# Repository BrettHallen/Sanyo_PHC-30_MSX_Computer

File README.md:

# Sanyo PHC-30 MSX Computer
Information about the 三洋 Sanyo PHC-30/PHC-30N computer.

## Specifications
- Sharp LH0080A Z80 CPU
- Fujitsu MB64H120 gate array (mask code Z03?)
- Mitsubishi M5L8255AP-5 peripheral interface (PPI)
- Hitachi HN613256P 32Kbit ROM (mask code Y00)
- General Instruments AY-3-8910 Programmable Sound Generator (PSG)
- 8 x Fujitsu MB8264A-15 64K x 1-bit main DRAM (64KB)
- TI TMS9118NL Video Display Processor (VDP)
- 2 x TI TMS4416-20NL 16K x 4-bit video DRAM (16KB)

## YouTube Videos
- [Part 1: Initial Look](https://youtu.be/X6lxfxol4aE)
- [Part 2: Pico9918 & Keyboard Refurbish](https://youtu.be/wInAnoi41x8)

## TMS9118 Replacement
I replaced the TMS9118 with a [Pico9918](https://github.com/visrealm/pico9918).  I had to de-solder the TMS9118 but it came out with a little gentle coaxing - I used my ENGINEER SS-03 Solder Sucker.<br>

There is one small issue: blank screen when doing a warm restart by pressing the RESET button but Troy has already sent me some test firmware to try out.<br>

## [Replacement Power Supply](/Sanyo_PHC-30_PSU)
My attempt at a "universal" 12VDC power supply to replace the original Japanese 100VAC power supply.<br>

The original power supply generates +5VDC and ±12VDC.<br>

My replacement generates the +5VDC and -12VDC via regulators and passes through the remaining 12VDC, so a good quality, regulated, 12VDC power supply rated at 3-4A should be used.<br>

It's currently pending testing.<br>

## [Images](/Images)
Images of the computer, motherboard & chips.

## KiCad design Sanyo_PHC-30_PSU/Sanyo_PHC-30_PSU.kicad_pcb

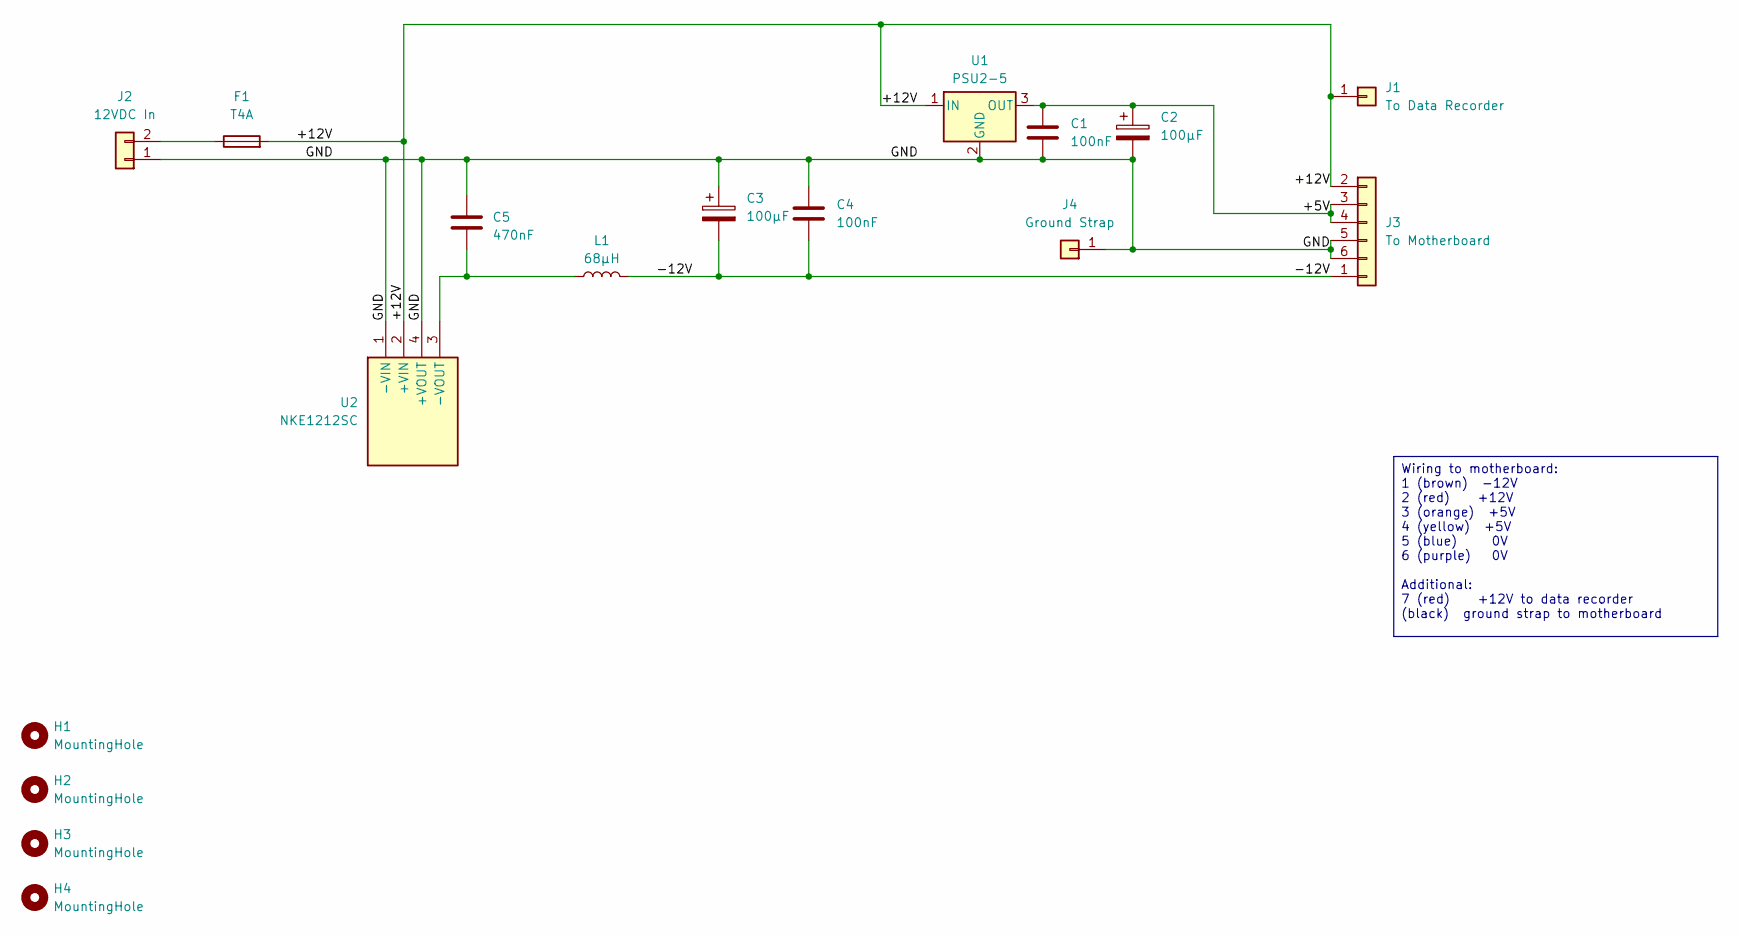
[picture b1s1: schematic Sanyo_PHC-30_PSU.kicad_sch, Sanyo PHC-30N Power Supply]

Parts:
C1, C4: 100nF; C_Disc_D3.4mm_W2.1mm_P2.50mm
C2, C3: 100µF; CP_Radial_D5.0mm_P2.50mm
C5: 470nF; C_Disc_D3.4mm_W2.1mm_P2.50mm
F1: T4A; Fuseholder_Clip-5x20mm_Littelfuse_111_Inline_P20.00x5.00mm_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
H1, H2, H3, H4: MountingHole; MountingHole_3.2mm_M3
J1: To Data Recorder; PinHeader_1x01_P2.54mm_Vertical
J2: 12VDC In; JST_VH_B2P-VH_1x02_P3.96mm_Vertical
J3: To Motherboard; JST_VH_B6P-VH_1x06_P3.96mm_Vertical
J4: Ground Strap; PinHeader_1x01_P2.54mm_Vertical
L1: 68µH; 22R683C
U1: PSU2-5; TO-220-3_Horizontal_TabDown
U2: NKE1212SC; Manufacturer_Part_Number NKE1212SC

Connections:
/+5V: C1.1, C2.1, J3.3 (+5V), J3.4 (+5V), U1.3 (OUT)
/+12V: F1.2, J1.1, J3.2 (+12V), U1.1 (IN), U2.2 (+VIN)
/-12V: C3.2, C4.2, J3.1 (-12V), L1.2
/GND: C1.2, C2.2, C3.1, C4.1, C5.2, J2.1, J3.5 (0V), J3.6 (0V), J4.1, U1.2 (GND), U2.1 (-VIN), U2.4 (+VOUT)
unnamed: F1.1, J2.2
unnamed: C5.1, L1.1, U2.3 (-VOUT)

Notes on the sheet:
Wiring to motherboard: 1 (brown) -12V 2 (red) +12V 3 (orange) +5V 4 (yellow) +5V 5 (blue) 0V 6 (purple) 0V Additional: 7 (red) +12V to data recorder (black) ground strap to motherboard

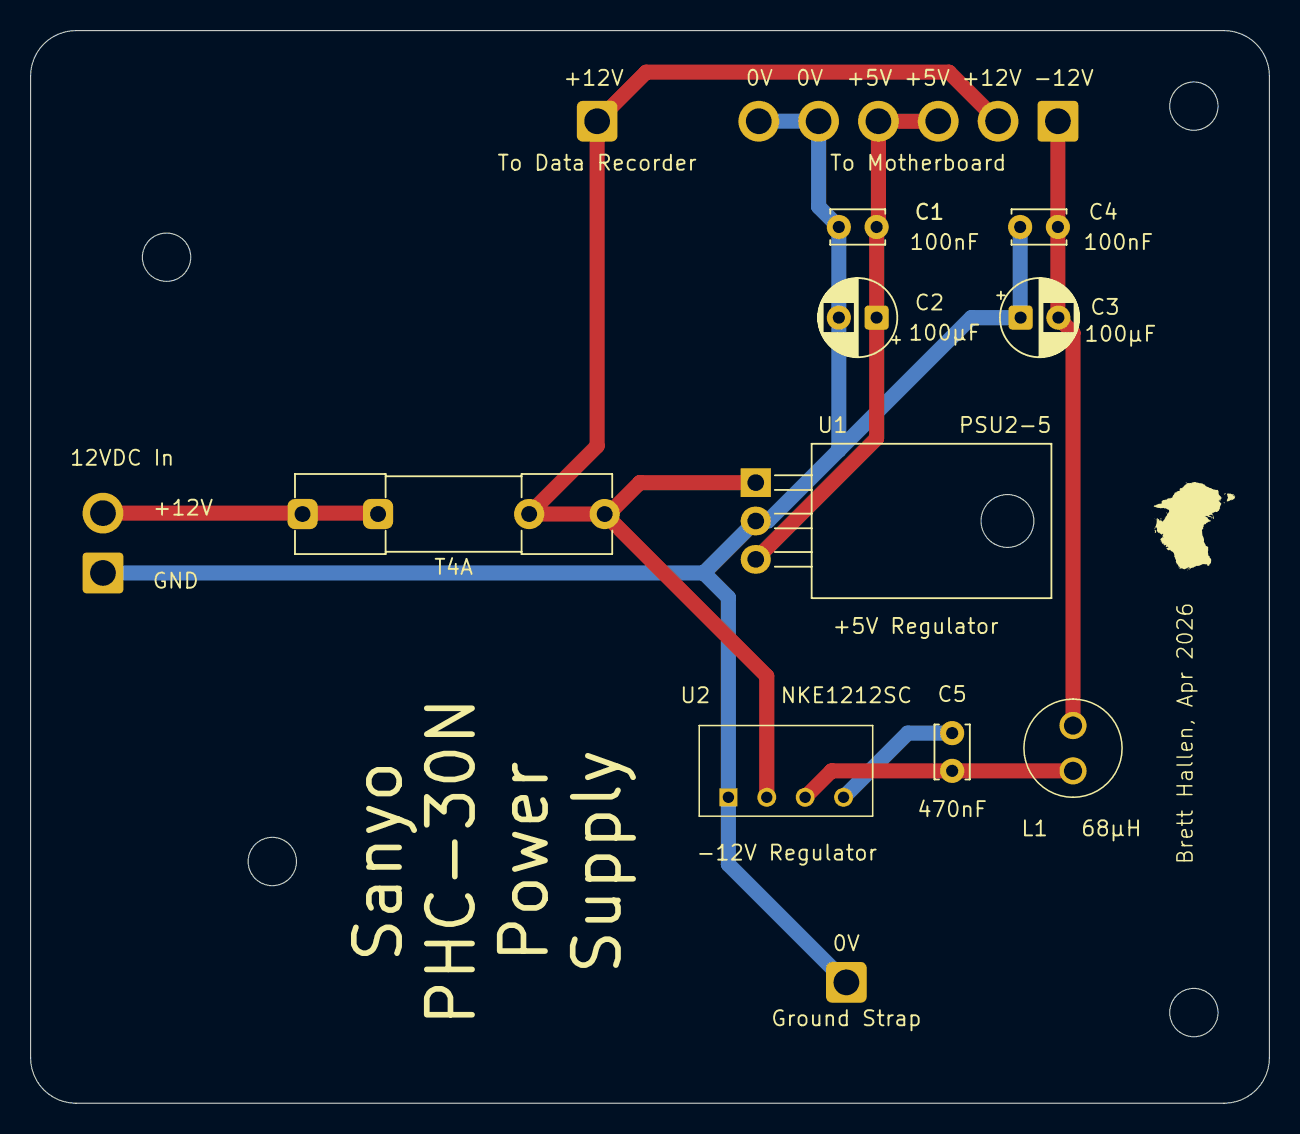
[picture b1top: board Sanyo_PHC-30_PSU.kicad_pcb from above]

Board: 2 copper layers, 82.0 x 71.0 mm, 17 parts (0 on the bottom side), 6 nets.

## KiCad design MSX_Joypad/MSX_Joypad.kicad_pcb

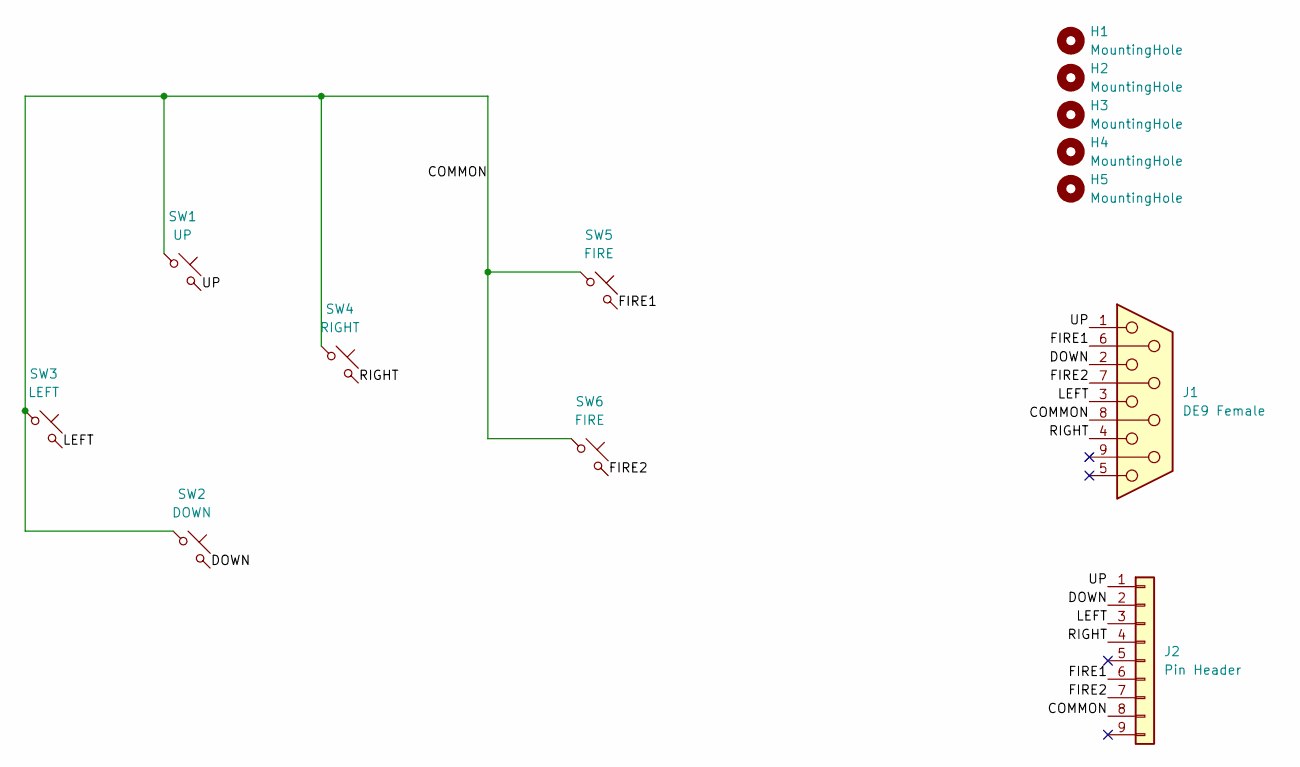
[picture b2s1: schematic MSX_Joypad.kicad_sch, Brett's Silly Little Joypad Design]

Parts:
H1, H2, H3, H4, H5: MountingHole; MountingHole_3.2mm_M3_DIN965
J1: DE9 Female; DSUB-9_Socket_EdgeMount_P2.77mm
J2: Pin Header; PinHeader_1x09_P2.54mm_Vertical
SW1: UP; SW_PUSH-12mm
SW2: DOWN; SW_PUSH-12mm
SW3: LEFT; SW_PUSH-12mm
SW4: RIGHT; SW_PUSH-12mm
SW5, SW6: FIRE; SW_PUSH-12mm

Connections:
/COMMON: J1.8, J2.8, SW1.1, SW2.1, SW3.1, SW4.1, SW5.1, SW6.1
/DOWN: J1.2, J2.2, SW2.2
/FIRE1: J1.6, J2.6, SW5.2
/FIRE2: J1.7, J2.7, SW6.2
/LEFT: J1.3, J2.3, SW3.2
/RIGHT: J1.4, J2.4, SW4.2
/UP: J1.1, J2.1, SW1.2

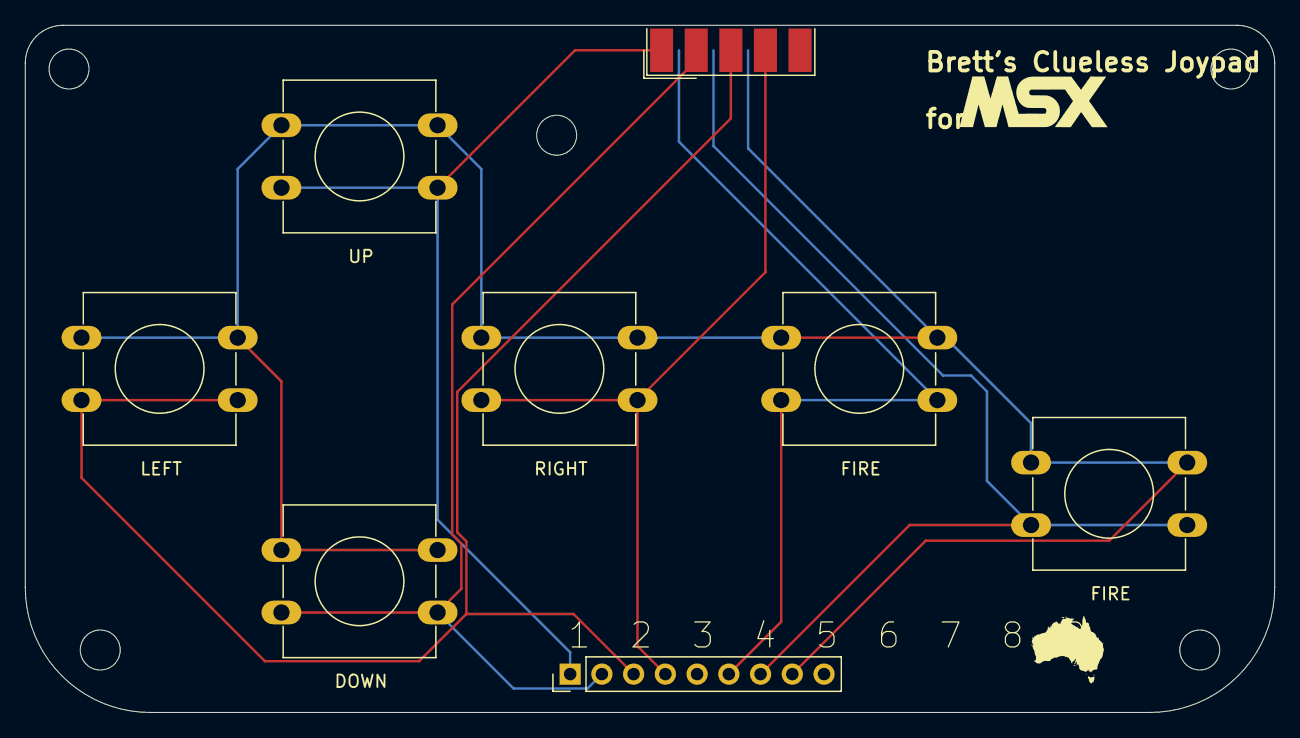
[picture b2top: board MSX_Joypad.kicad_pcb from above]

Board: 2 copper layers, 100.0 x 55.0 mm, 13 parts (0 on the bottom side), 7 nets.

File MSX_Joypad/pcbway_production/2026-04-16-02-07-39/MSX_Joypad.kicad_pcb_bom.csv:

Designator,Quantity,Value,Footprint,Package,MPN,DNP,Mount_Type,Description
J1,1,DE9 Female,DSUB-9_Socket_EdgeMount_P2.77mm,,,,smt,"9-pin D-SUB connector, socket (female)"
J2,1,Pin Header,PinHeader_1x09_P2.54mm_Vertical,,,,tht,"Generic connector, single row, 01x09, script generated (kicad-library-utils/schlib/autogen/connector/)"
SW1,1,UP,SW_PUSH-12mm,,,,tht,"Push button switch, normally open, two pins, 45° tilted"
SW2,1,DOWN,SW_PUSH-12mm,,,,tht,"Push button switch, normally open, two pins, 45° tilted"
SW3,1,LEFT,SW_PUSH-12mm,,,,tht,"Push button switch, normally open, two pins, 45° tilted"
SW4,1,RIGHT,SW_PUSH-12mm,,,,tht,"Push button switch, normally open, two pins, 45° tilted"
"SW5, SW6",2,FIRE,SW_PUSH-12mm,,,,tht,"Push button switch, normally open, two pins, 45° tilted"

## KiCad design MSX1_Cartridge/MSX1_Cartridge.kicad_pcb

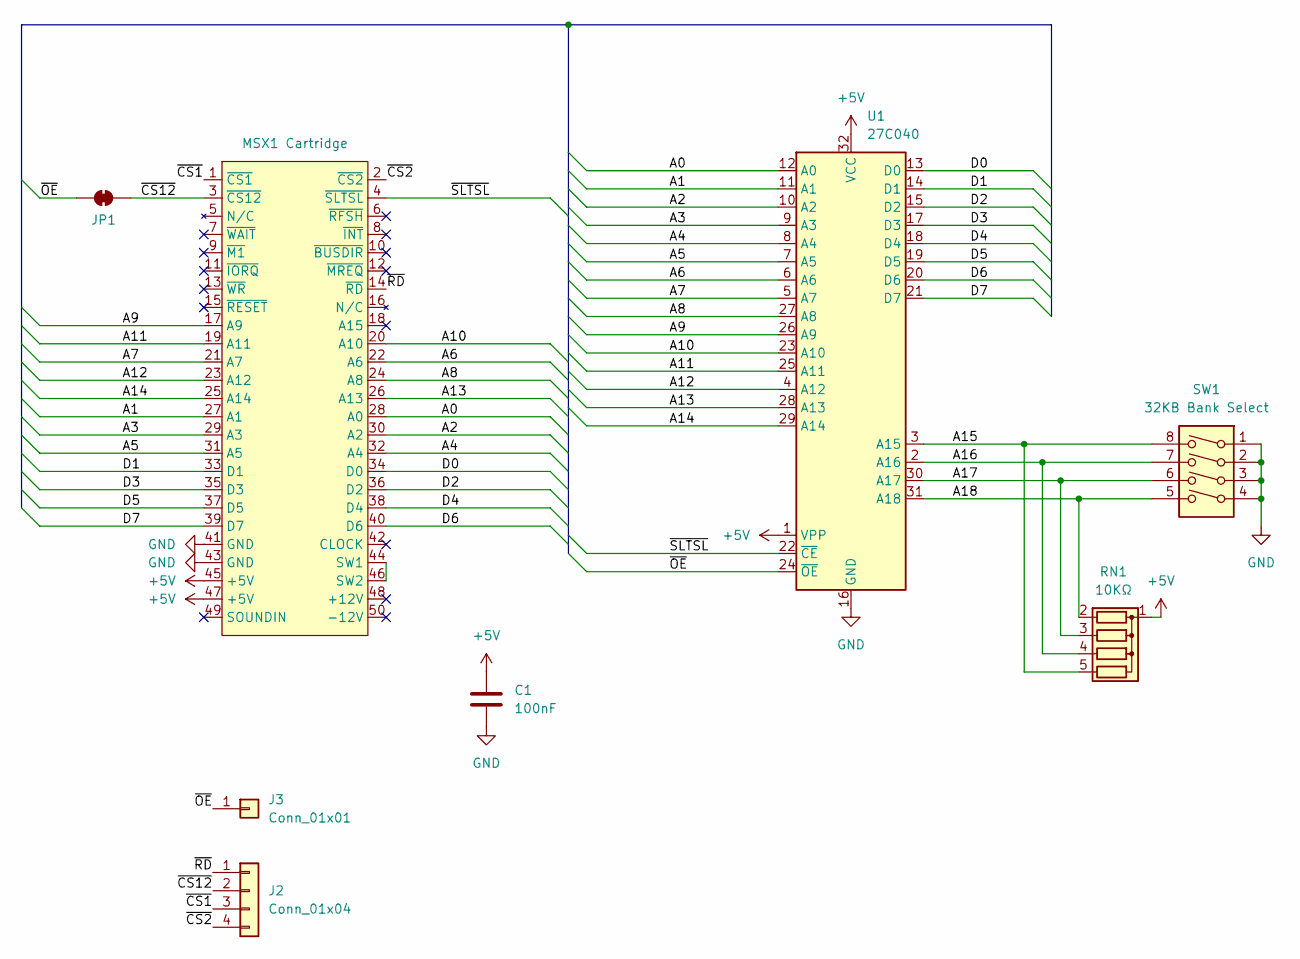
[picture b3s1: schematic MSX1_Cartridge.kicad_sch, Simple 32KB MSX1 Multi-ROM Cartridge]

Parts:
C1: 100nF; C_Disc_D3.4mm_W2.1mm_P2.50mm
J1: MSX1 Cartridge
J2: Conn_01x04; PinHeader_1x04_P2.54mm_Vertical
J3: Conn_01x01; PinHeader_1x01_P2.54mm_Vertical
JP1: ~{OE}; SolderJumper-2_P1.3mm_Bridged_RoundedPad1.0x1.5mm
RN1: 10KΩ; R_Array_SIP5
SW1: 32KB Bank Select; SW_DIP_SPSTx04_Slide_9.78x12.34mm_W7.62mm_P2.54mm
U1: 27C040; DIP-32_W15.24mm_Socket_LongPads

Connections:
+5V: C1.1, J1.45 (+5V), J1.47 (+5V), RN1.1 (common), U1.1 (VPP), U1.32 (VCC)
/A0: J1.28 (A0), U1.12 (A0)
/A1: J1.27 (A1), U1.11 (A1)
/A2: J1.30 (A2), U1.10 (A2)
/A3: J1.29 (A3), U1.9 (A3)
/A4: J1.32 (A4), U1.8 (A4)
/A5: J1.31 (A5), U1.7 (A5)
/A6: J1.22 (A6), U1.6 (A6)
/A7: J1.21 (A7), U1.5 (A7)
/A8: J1.24 (A8), U1.27 (A8)
/A9: J1.17 (A9), U1.26 (A9)
/A10: J1.20 (A10), U1.23 (A10)
/A11: J1.19 (A11), U1.25 (A11)
/A12: J1.23 (A12), U1.4 (A12)
/A13: J1.26 (A13), U1.28 (A13)
/A14: J1.25 (A14), U1.29 (A14)
/A15: RN1.5 (R4), SW1.8, U1.3 (A15)
/A16: RN1.4 (R3), SW1.7, U1.2 (A16)
/A17: RN1.3 (R2), SW1.6, U1.30 (A17)
/A18: RN1.2 (R1), SW1.5, U1.31 (A18)
/D0: J1.34 (D0), U1.13 (D0)
/D1: J1.33 (D1), U1.14 (D1)
/D2: J1.36 (D2), U1.15 (D2)
/D3: J1.35 (D3), U1.17 (D3)
/D4: J1.38 (D4), U1.18 (D4)
/D5: J1.37 (D5), U1.19 (D5)
/D6: J1.40 (D6), U1.20 (D6)
/D7: J1.39 (D7), U1.21 (D7)
/~CS1: J1.1 (~CS1), J2.3
/~CS2: J1.2 (~CS2), J2.4
/~CS12: J1.3 (~CS12), J2.2, JP1.2 (B)
/~OE: J3.1, JP1.1 (A), U1.24 (~OE)
/~RD: J1.14 (~RD), J2.1
/~SLTSL: J1.4 (~SLTSL), U1.22 (~CE)
GND: C1.2, J1.41 (GND), J1.43 (GND), SW1.1, SW1.2, SW1.3, SW1.4, U1.16 (GND)
unnamed: J1.44 (SW1), J1.46 (SW2)

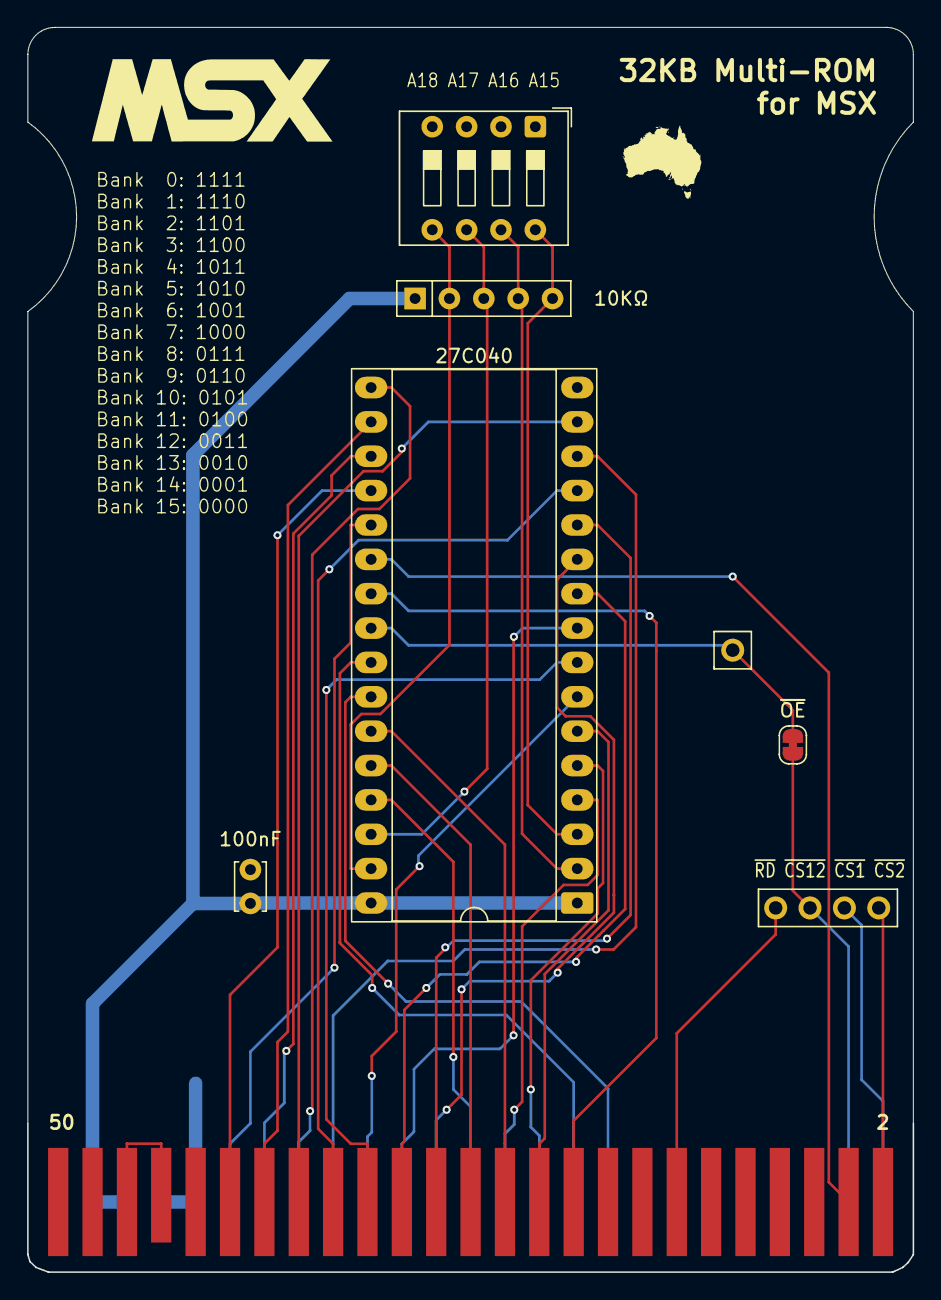
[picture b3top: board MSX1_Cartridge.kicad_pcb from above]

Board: 2 copper layers, 65.5 x 92.0 mm, 8 parts (0 on the bottom side), 36 nets.

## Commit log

2026-04-12 PCB cosmetic change
2026-05-13 Fixed C3 orientation
    +ve leg of electrolytic should be connected to GND and -ve leg to -12V ... GND is more positive than -12V, duh
